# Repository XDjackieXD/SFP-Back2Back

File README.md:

# SFP+ Back2Back

This is a simple board to connect two SFP/SFP+ modules together.

So far it has only been tested with 10G fiber transceivers.
While it should work with other 1G and 10G (and maybe even 25G) modules and DACs too, I have not tested it with those (and I know that DACs tend to be more of an issue with such passive adapters/extenders).

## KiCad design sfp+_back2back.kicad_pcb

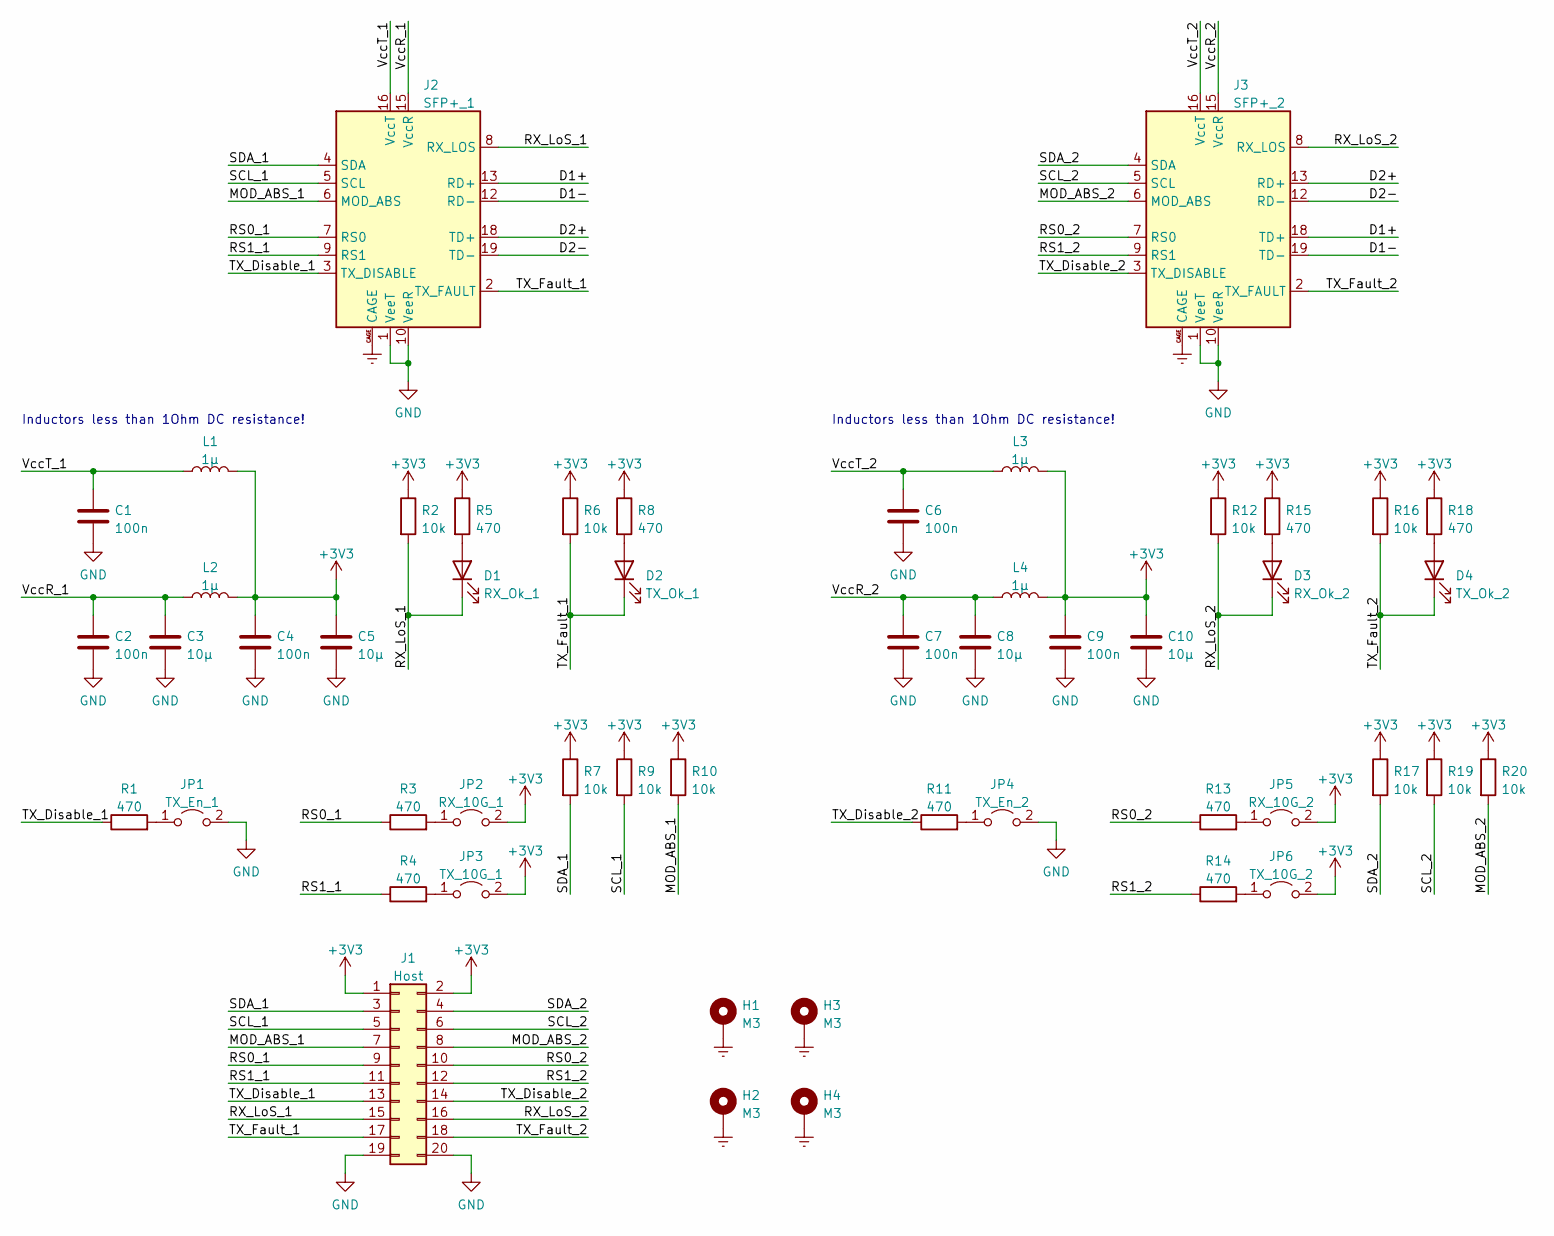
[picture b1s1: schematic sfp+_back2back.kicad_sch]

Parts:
C1, C2, C4, C6, C7, C9: 100n; C_0603_1608Metric_Pad1.08x0.95mm_HandSolder
C3, C5, C8, C10: 10µ; C_0805_2012Metric_Pad1.18x1.45mm_HandSolder
D1: RX_Ok_1; LED_0805_2012Metric_Pad1.15x1.40mm_HandSolder
D2: TX_Ok_1; LED_0805_2012Metric_Pad1.15x1.40mm_HandSolder
D3: RX_Ok_2; LED_0805_2012Metric_Pad1.15x1.40mm_HandSolder
D4: TX_Ok_2; LED_0805_2012Metric_Pad1.15x1.40mm_HandSolder
H1, H2, H3, H4: M3; MountingHole_3.2mm_M3_Pad_Via
J1: Host; PinHeader_2x10_P2.54mm_Vertical
J2: SFP+_1; Connector_SFP_and_Cage
J3: SFP+_2; Connector_SFP_and_Cage
JP1: TX_En_1; PinHeader_1x02_P2.54mm_Vertical
JP2: RX_10G_1; PinHeader_1x02_P2.54mm_Vertical
JP3: TX_10G_1; PinHeader_1x02_P2.54mm_Vertical
JP4: TX_En_2; PinHeader_1x02_P2.54mm_Vertical
JP5: RX_10G_2; PinHeader_1x02_P2.54mm_Vertical
JP6: TX_10G_2; PinHeader_1x02_P2.54mm_Vertical
L1, L2, L3, L4: 1µ; L_0805_2012Metric_Pad1.15x1.40mm_HandSolder
R1, R3, R4, R5, R8, R11, R13, R14, R15, R18: 470; R_0603_1608Metric_Pad0.98x0.95mm_HandSolder
R2, R6, R7, R9, R10, R12, R16, R17, R19, R20: 10k; R_0603_1608Metric_Pad0.98x0.95mm_HandSolder

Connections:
+3V3: C4.1, C5.1, C9.1, C10.1, J1.1, J1.2, JP2.2 (B), JP3.2 (B), JP5.2 (B), JP6.2 (B), L1.2, L2.2, L3.2, L4.2, R2.1, R5.1, R6.1, R7.1, R8.1, R9.1, R10.1, R12.1, R15.1, R16.1, R17.1, R18.1, R19.1, R20.1
/D1+: J2.13 (RD+), J3.18 (TD+)
/D1-: J2.12 (RD-), J3.19 (TD-)
/D2+: J2.18 (TD+), J3.13 (RD+)
/D2-: J2.19 (TD-), J3.12 (RD-)
/MOD_ABS_1: J1.7, J2.6 (MOD_ABS), R10.2
/MOD_ABS_2: J1.8, J3.6 (MOD_ABS), R20.2
/RS0_1: J1.9, J2.7 (RS0), R3.1
/RS0_2: J1.10, J3.7 (RS0), R13.1
/RS1_1: J1.11, J2.9 (RS1), R4.1
/RS1_2: J1.12, J3.9 (RS1), R14.1
/RX_LoS_1: D1.1 (K), J1.15, J2.8 (RX_LOS), R2.2
/RX_LoS_2: D3.1 (K), J1.16, J3.8 (RX_LOS), R12.2
/SCL_1: J1.5, J2.5 (SCL), R9.2
/SCL_2: J1.6, J3.5 (SCL), R19.2
/SDA_1: J1.3, J2.4 (SDA), R7.2
/SDA_2: J1.4, J3.4 (SDA), R17.2
/TX_Disable_1: J1.13, J2.3 (TX_DISABLE), R1.1
/TX_Disable_2: J1.14, J3.3 (TX_DISABLE), R11.1
/TX_Fault_1: D2.1 (K), J1.17, J2.2 (TX_FAULT), R6.2
/TX_Fault_2: D4.1 (K), J1.18, J3.2 (TX_FAULT), R16.2
/VccR_1: C2.1, C3.1, J2.15 (VccR), L2.1
/VccR_2: C7.1, C8.1, J3.15 (VccR), L4.1
/VccT_1: C1.1, J2.16 (VccT), L1.1
/VccT_2: C6.1, J3.16 (VccT), L3.1
Earth: H1.1, H2.1, H3.1, H4.1, J2.CAGE, J3.CAGE
GND: C1.2, C2.2, C3.2, C4.2, C5.2, C6.2, C7.2, C8.2, C9.2, C10.2, J1.19, J1.20, J2.1 (VeeT), J2.10 (VeeR), J2.11 (VeeR), J2.14 (VeeR), J2.17 (VeeT), J2.20 (VeeT), J3.1 (VeeT), J3.10 (VeeR), J3.11 (VeeR), J3.14 (VeeR), J3.17 (VeeT), J3.20 (VeeT), JP1.2 (B), JP4.2 (B)
unnamed: D1.2 (A), R5.2
unnamed: D2.2 (A), R8.2
unnamed: D3.2 (A), R15.2
unnamed: D4.2 (A), R18.2
unnamed: JP1.1 (A), R1.2
unnamed: JP2.1 (A), R3.2
unnamed: JP3.1 (A), R4.2
unnamed: JP4.1 (A), R11.2
unnamed: JP5.1 (A), R13.2
unnamed: JP6.1 (A), R14.2

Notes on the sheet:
Inductors less than 1Ohm DC resistance!

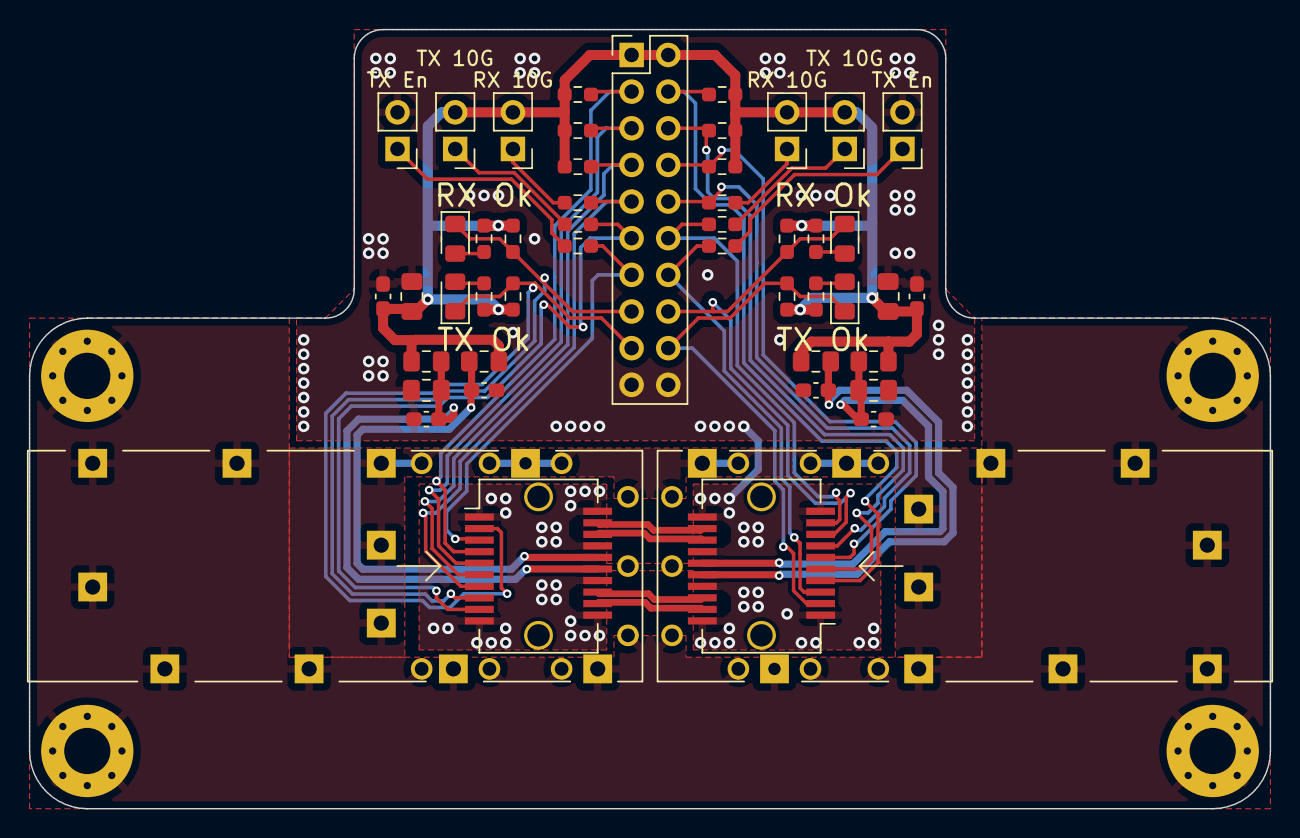
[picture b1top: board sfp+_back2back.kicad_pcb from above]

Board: 2 copper layers, 86.0 x 54.0 mm, 51 parts (0 on the bottom side), 37 nets.

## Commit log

2023-10-12 feat: initial commit
2023-10-12 feat: add image
